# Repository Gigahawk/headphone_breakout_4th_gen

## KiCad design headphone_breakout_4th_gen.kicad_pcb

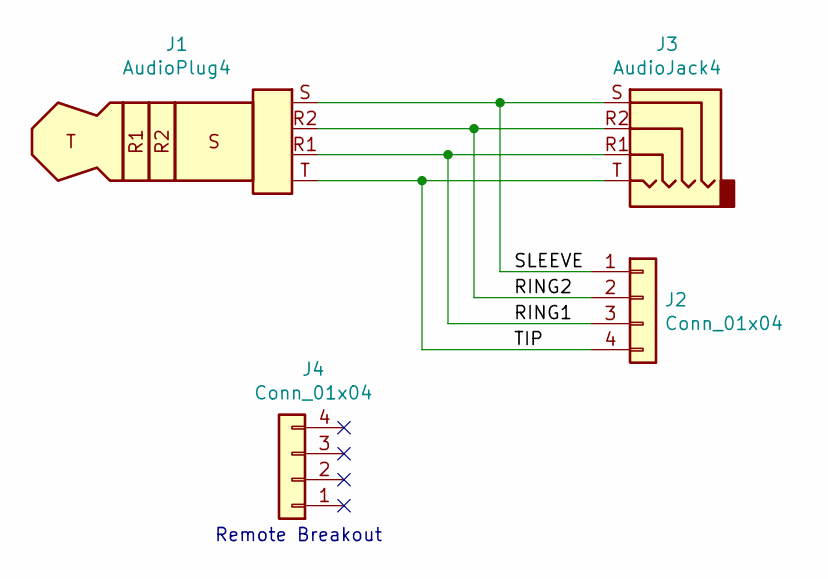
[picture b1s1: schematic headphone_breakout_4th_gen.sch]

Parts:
J1: AudioPlug4; 54-00035
J2: Conn_01x04; PinHeader_1x04_P2.54mm_Vertical
J3: AudioJack4; 54-00174
J4: Conn_01x04; IPOD_4TH_REMOTE_BREAKOUT

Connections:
/RING1: J1.R1, J2.3, J3.R1
/RING2: J1.R2, J2.2, J3.R2
/SLEEVE: J1.S, J2.1, J3.S
/TIP: J1.T, J2.4, J3.T

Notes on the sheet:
Remote Breakout

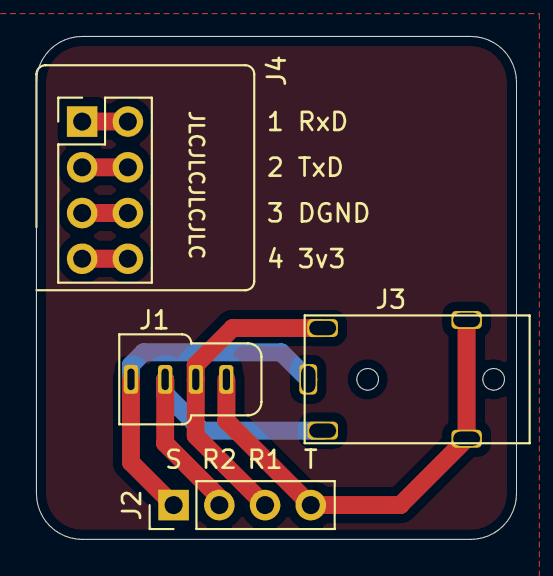
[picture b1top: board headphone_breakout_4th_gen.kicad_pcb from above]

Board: 2 copper layers, 26.7 x 27.9 mm, 4 parts (0 on the bottom side), 4 nets.

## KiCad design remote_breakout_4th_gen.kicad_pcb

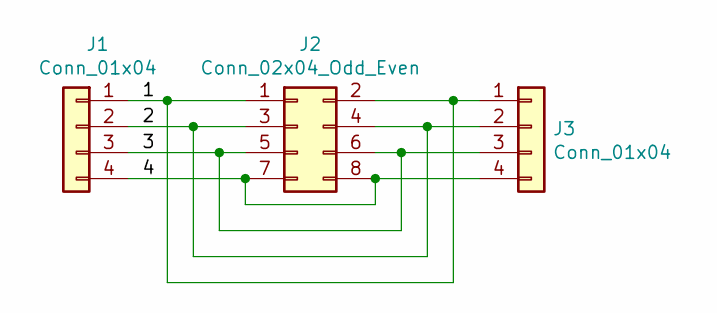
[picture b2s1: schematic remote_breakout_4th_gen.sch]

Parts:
J1: Conn_01x04; IPOD_4TH_REMOTE
J2: Conn_02x04_Odd_Even; PinHeader_2x04_P2.54mm_Vertical
J3: Conn_01x04; PinHeader_1x04_P2.54mm_Vertical

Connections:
/1: J1.1, J2.1, J2.2, J3.1
/2: J1.2, J2.3, J2.4, J3.2
/3: J1.3, J2.5, J2.6, J3.3
/4: J1.4, J2.7, J2.8, J3.4

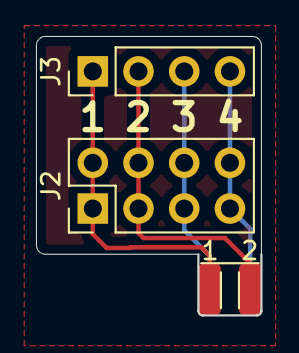
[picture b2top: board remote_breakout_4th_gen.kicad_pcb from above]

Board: 2 copper layers, 12.5 x 15.5 mm, 3 parts (0 on the bottom side), 4 nets.

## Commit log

2021-01-11 First commit, finalize board geometry
2021-03-14 Fill unused areas with copper, update remote connector with connector pads
2021-04-01 Prepare for JLCPCB
2021-04-22 Add labels for remote connector
